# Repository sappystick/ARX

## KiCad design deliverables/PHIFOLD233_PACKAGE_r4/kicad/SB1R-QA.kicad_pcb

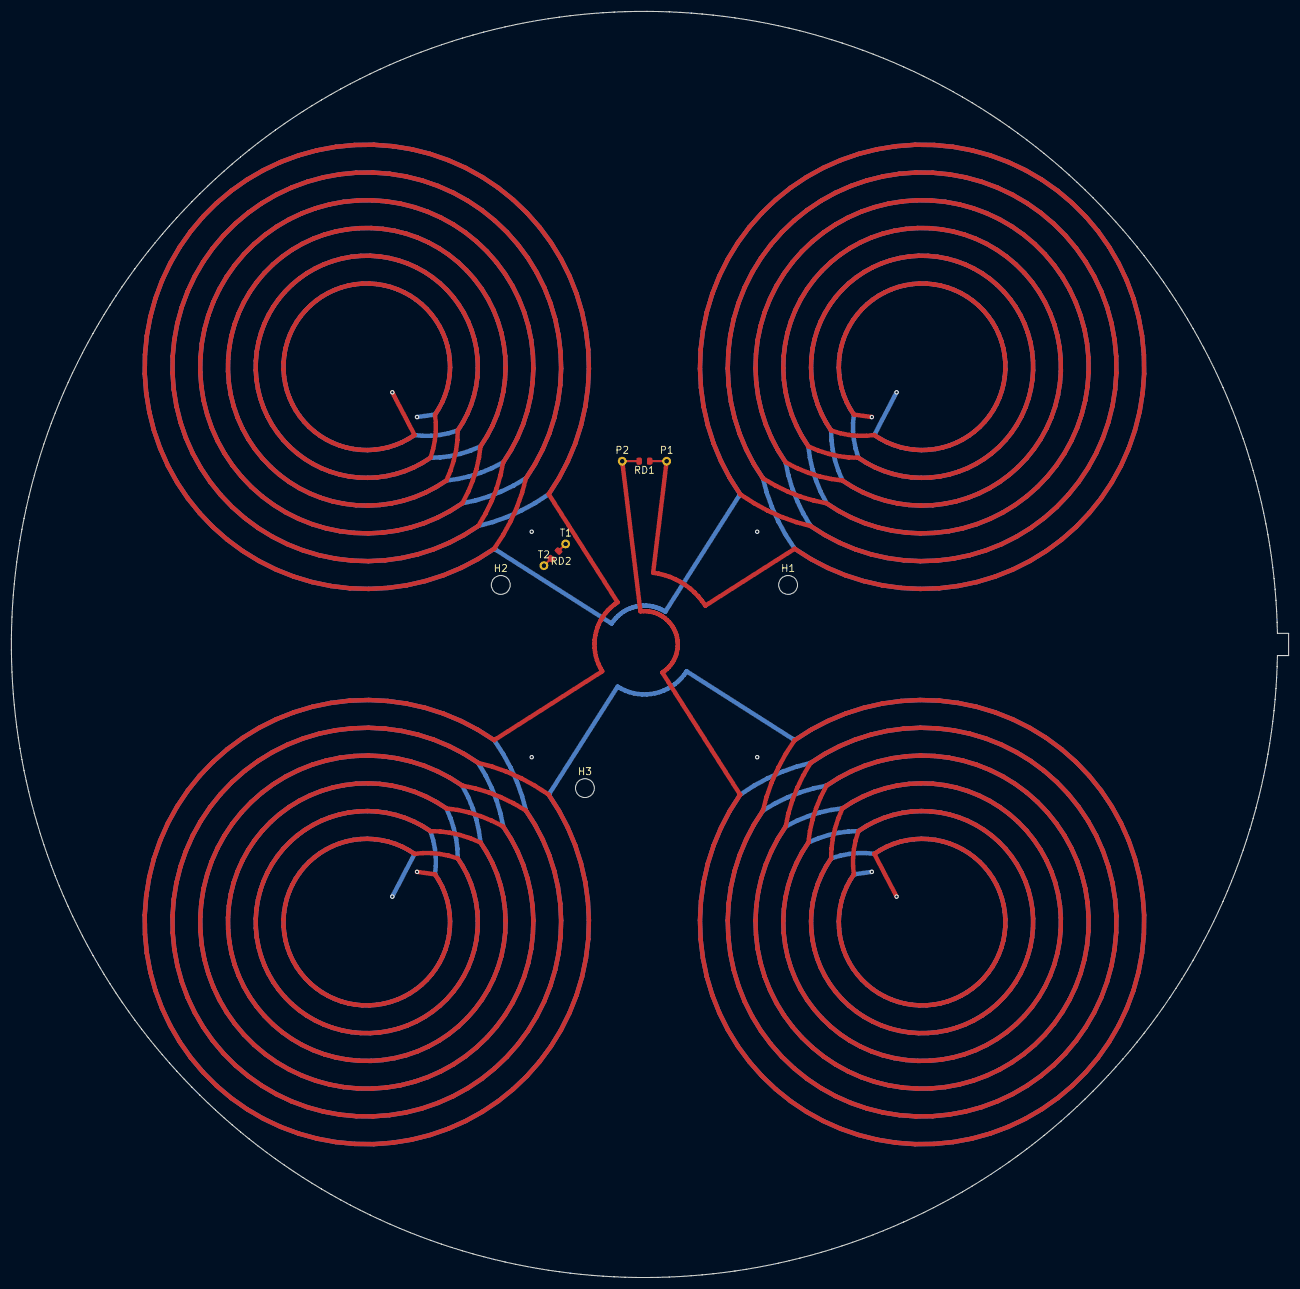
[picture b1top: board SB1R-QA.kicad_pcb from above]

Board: 4 copper layers, 230.0 x 228.0 mm, 9 parts (0 on the bottom side), 3 nets.

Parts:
H1, H2, H3: MH_M3
P1, P2: LEAD_PAD
RD1, RD2: 680R 0.1% thin film 0805, non-magnetic terminatio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; R_0805_2012Metric
T1, T2: TRANSFER_PAD

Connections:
QA_COIL: P1.1, P2.1, RD1.1, RD1.2
QB_T1: RD2.1, T1.1
QB_T2: RD2.2, T2.1

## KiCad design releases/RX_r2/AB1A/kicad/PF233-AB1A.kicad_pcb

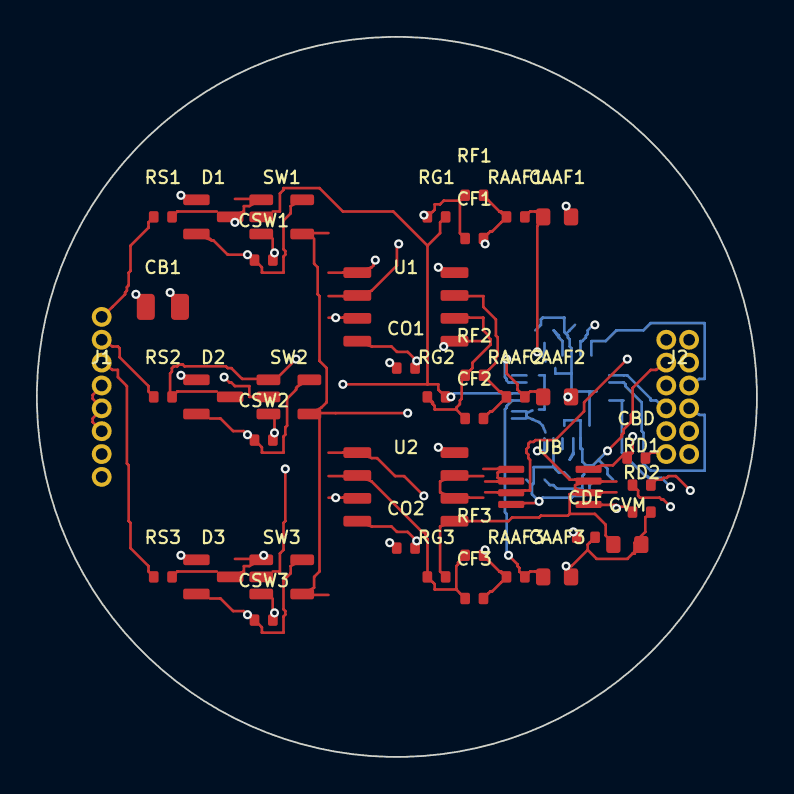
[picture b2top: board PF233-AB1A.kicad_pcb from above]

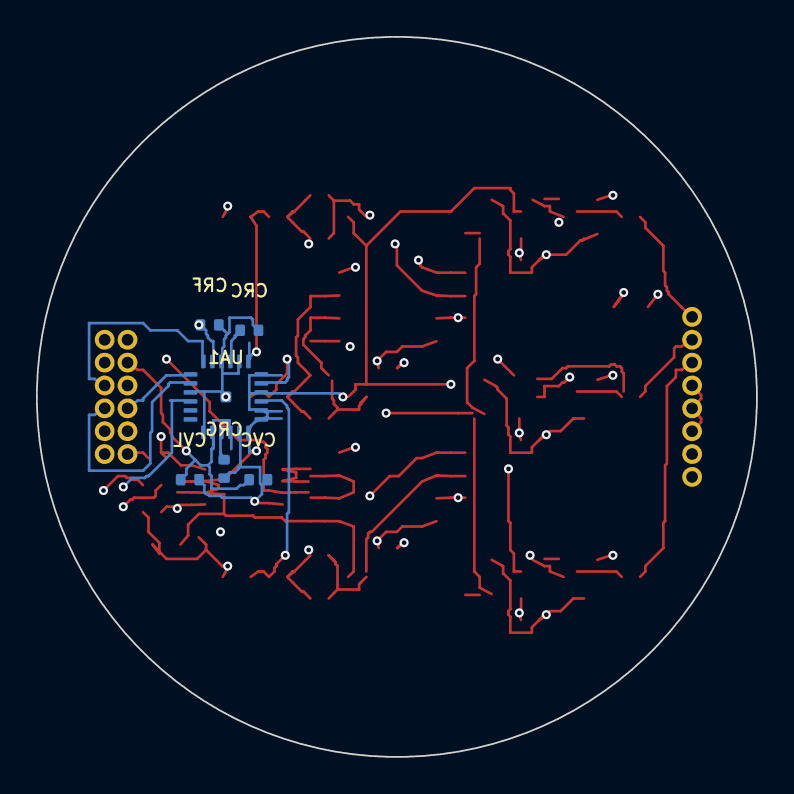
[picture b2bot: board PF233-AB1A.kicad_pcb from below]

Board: 6 copper layers, 40.0 x 40.0 mm, 46 parts (6 on the bottom side), 30 nets.

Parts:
CAAF1, CAAF2, CAAF3: 2n2; C_0603_1608Metric
CB1: 10u; C_0805_2012Metric
CBD: 100n; C_0402_1005Metric
CDF: 100n; C_0402_1005Metric
CF1, CF2, CF3: 22p; C_0402_1005Metric
CO1, CO2: 100n; C_0402_1005Metric
CRC: 100n; C_0402_1005Metric
CRF: 1u; C_0402_1005Metric
CRG: 1u; C_0402_1005Metric
CSW1, CSW2, CSW3: 100n; C_0402_1005Metric
CVC: 1u; C_0402_1005Metric
CVL: 1u; C_0402_1005Metric
CVM: 1u; C_0603_1608Metric
D1, D2, D3: BAV199; SOT-23
J1: Antenna harness 8p solder pads 1.27mm; PinHeader_1x8_P1.27mm
J2: Main-board 2x6 1.27mm header; PinHeader_2x6_P1.27mm
RAAF1, RAAF2, RAAF3: 200; R_0402_1005Metric
RD1, RD2: 100k; R_0402_1005Metric
RF1, RF2, RF3: 390; R_0402_1005Metric
RG1, RG2, RG3: 10; R_0402_1005Metric
RS1, RS2: 100; R_0402_1005Metric
RS3: 1000; R_0402_1005Metric
SW1, SW2, SW3: 74LVC1G66; SOT-23-5
U1, U2: OPA2211; SOIC-8_3.9x4.9mm_P1.27mm
UA1: AD7389-4; CP-24-25_ADI_LFCSP-24-1EP_4x4mm_P0.5mm_EP0.61x0.61mm
UB: OPA2365; MSOP-8_3x3mm_P0.65mm

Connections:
+3V3D: CVC.1, CVL.1, J2.3, UA1.2, UA1.4
+5VA: CB1.1, CBD.1, CO1.1, CO2.1, CSW1.1, CSW2.1, CSW3.1, D1.2, D2.2, D3.2, J2.1, SW1.5, SW2.5, SW3.5, U1.8, U2.8, UB.8
ADCIN_GX: CAAF1.1, RAAF1.2, UA1.13
ADCIN_GY: CAAF2.1, RAAF2.2, UA1.11
ADCIN_X8: CAAF3.1, RAAF3.2, UA1.9
BLANK: J2.10, SW1.4, SW2.4, SW3.4
CS: J2.6, UA1.18
FB_GX: CF1.1, RF1.1, RG1.1, U1.2
FB_GY: CF2.1, RF2.1, RG2.1, U1.6
FB_X8: CF3.1, RF3.1, RG3.1, U2.2
GND: CAAF1.2, CAAF2.2, CAAF3.2, CB1.2, CBD.2, CDF.2, CO1.2, CO2.2, CRC.2, CRF.2, CRG.2, CSW1.2, CSW2.2, CSW3.2, CVC.2, CVL.2, CVM.2, D1.1, D2.1, D3.1, J1.7, J1.8, J2.2, J2.4, J2.11, J2.12, RD2.2, SW1.3, SW2.3, SW3.3, U1.4, U2.4, UA1.1, UA1.5, UA1.14, UA1.16, UA1.21, UA1.25, UB.4
IN_GX: D1.3, RS1.2, SW1.1, U1.3
IN_GY: D2.3, RS2.2, SW2.1, U1.5
IN_X8: D3.3, RS3.2, SW3.1, U2.3
OUT_GX: CF1.2, RAAF1.1, RF1.2, U1.1
OUT_GY: CF2.2, RAAF2.1, RF2.2, U1.7
OUT_X8: CF3.2, RAAF3.1, RF3.2, U2.1
RAW_GX: J1.1, RS1.1
RAW_GY: J1.2, RS2.1
RAW_X8: J1.3, RS3.1
REFCAP: CRC.1, UA1.15
REGCAP: CRG.1, UA1.3
SCLK: J2.5, UA1.22
SDO1: J2.7, UA1.19
SDO2: J2.8, UA1.20
SPARE_OUT_U2: U2.6, U2.7
VCM: CVM.1, J1.4, J1.5, J1.6, RG1.2, RG2.2, RG3.2, SW1.2, SW2.2, SW3.2, U2.5, UA1.6, UA1.7, UA1.8, UA1.10, UA1.12, UB.6, UB.7
VCM_DIV: CDF.1, RD1.2, RD2.1, UB.5
VREF: UB.1, UB.2
VREF_RAW: CRF.1, RD1.1, UA1.17, UB.3

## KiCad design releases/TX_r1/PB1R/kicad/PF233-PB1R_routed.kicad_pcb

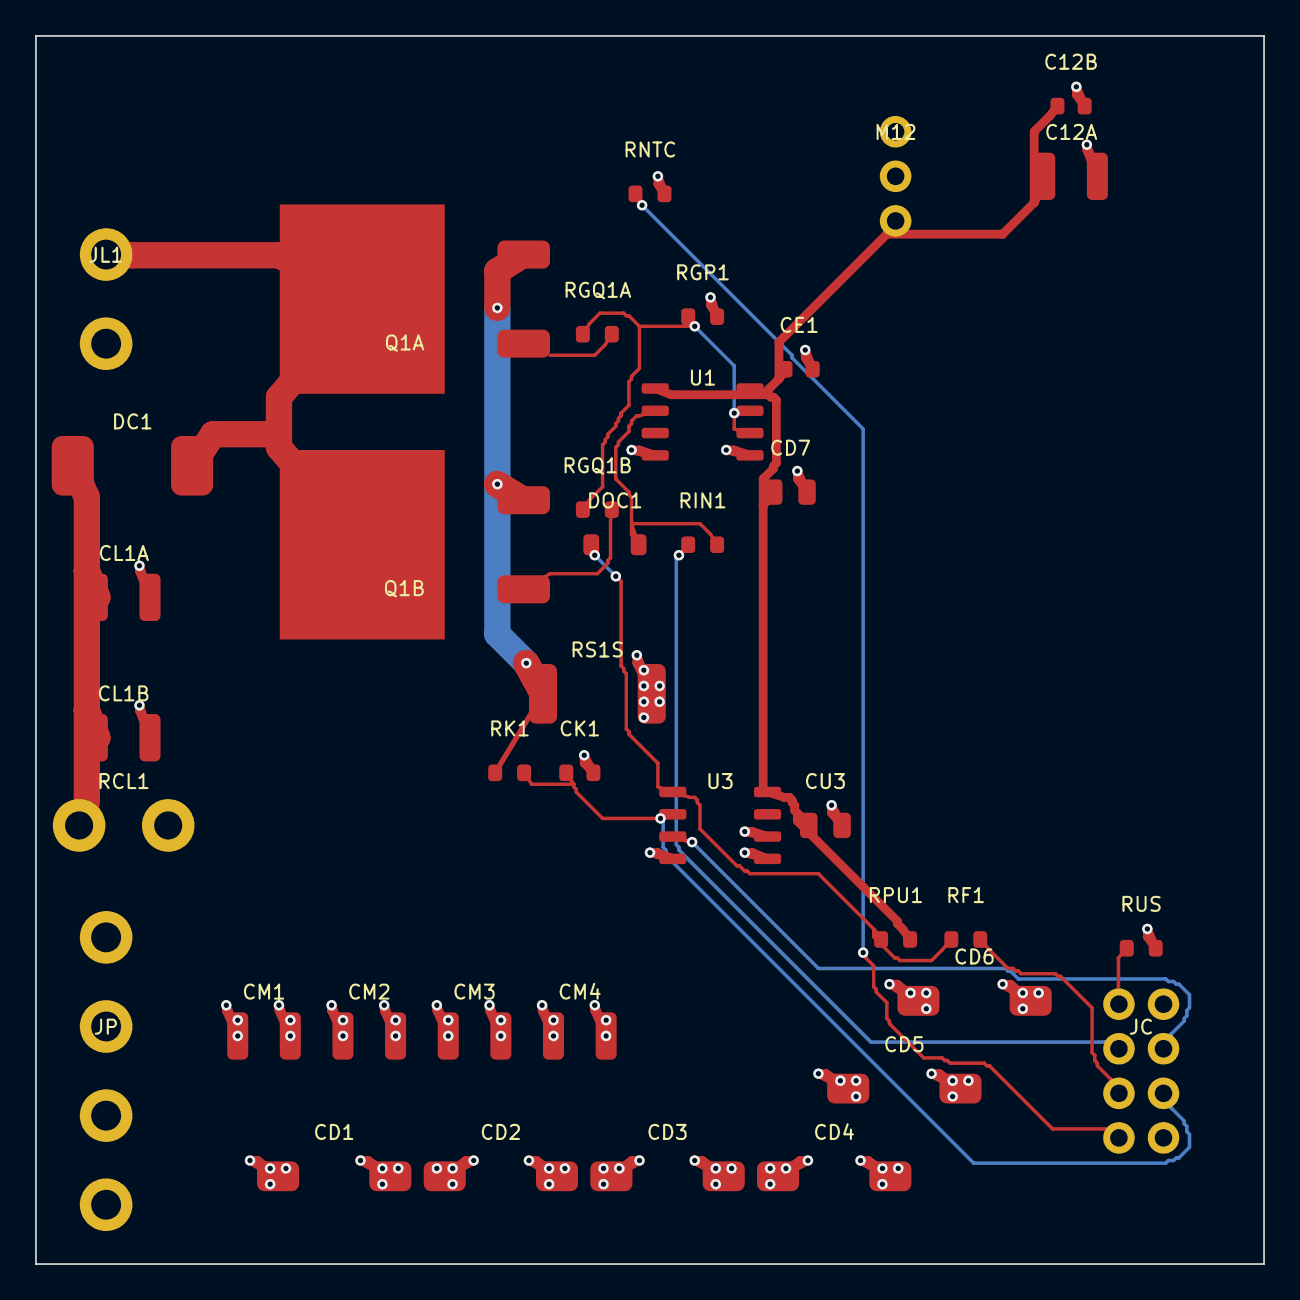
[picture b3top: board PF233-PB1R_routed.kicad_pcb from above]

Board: 4 copper layers, 70.0 x 70.0 mm, 39 parts (0 on the bottom side), 17 nets.

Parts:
C12A: 22u 25V; C_1210_3225Metric
C12B: 100n; C_0603_1608Metric
CD1, CD2, CD3, CD4, CD5, CD6: 150u 50V polymer Ta; CP_EIA-7343-43_Kemet-X
CD7: 1u 25V; C_0805_2012Metric
CE1: 100n; C_0603_1608Metric
CK1: 100p; C_0603_1608Metric
CL1A, CL1B: 100n 630V; C_1210_3225Metric
CM1, CM2, CM3, CM4: 10u 50V; C_1210_3225Metric
CU3: 1u 25V; C_0805_2012Metric
DC1: ES3J 600V 3A; D_SMC
DOC1: BAS16; D_SOD-123
JC: Umbilical from the head: SHLD GND TX1_IN REF_I1 F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; Pin_header_2x4_P2.54mm
JL1: Coil outer band: DRAIN, VBUS; Terminal_block_1x2_P5.08mm
JP: Power in: VBUS VBUS GND GND; Terminal_block_1x4_P5.08mm
M12: 12 V 1.5 A switching module; Converter_DCDC_Murata_OKI-78SR_Horizontal
Q1A, Q1B: 650V SJ 95mR; TO-263-3_TabPin2
RCL1: external 5k 10W (lid bank); SolderPad_2x_P5.08mm
RF1: 1k; R_0603_1608Metric
RGP1: 10k; R_0603_1608Metric
RGQ1A, RGQ1B: 10; R_0603_1608Metric
RIN1: 100; R_0603_1608Metric
RK1: 100; R_0603_1608Metric
RNTC: 10k NTC; R_0603_1608Metric
RPU1: 10k; R_0603_1608Metric
RS1S: 10m 3W; R_2512_6332Metric
RUS: 1M; R_0603_1608Metric
U1: TC4420; SOIC-8_3.9x4.9mm_P1.27mm
U3: LM393; SOIC-8_3.9x4.9mm_P1.27mm

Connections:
AUX12: C12A.1, C12B.1, CD7.1, CE1.1, CU3.1, M12.3, RPU1.2, U1.1, U1.8, U3.8
CLAMP1: CL1A.1, CL1B.1, DC1.1, RCL1.1
DRAIN1: DC1.2, JL1.1, Q1A.2, Q1B.2
DRVIN1: DOC1.2, RIN1.2, U1.2
FAULT1_N: JC.5, RF1.2
G1: RGP1.1, RGQ1A.1, RGQ1B.1, U1.6, U1.7
GATE_Q1A: Q1A.1, RGQ1A.2
GATE_Q1B: Q1B.1, RGQ1B.2
GND: C12A.2, C12B.2, CD1.2, CD2.2, CD3.2, CD4.2, CD5.2, CD6.2, CD7.2, CE1.2, CK1.2, CM1.2, CM2.2, CM3.2, CM4.2, CU3.2, JC.2, JC.8, JP.3, JP.4, M12.2, RGP1.2, RNTC.2, RS1S.2, RUS.2, U1.4, U1.5, U3.4, U3.5, U3.6
ISENSE1: CK1.1, JC.6, RK1.2, U3.2
NTC_SENSE: JC.7, RNTC.1
OC1_OUT: DOC1.1, RF1.1, RPU1.1, U3.1
REF_I1: JC.4, U3.3
SRC1: Q1A.3, Q1B.3, RK1.1, RS1S.1
TX1_IN: JC.3, RIN1.1
UMB_SHLD: JC.1, RUS.1
VBUS: CD1.1, CD2.1, CD3.1, CD4.1, CD5.1, CD6.1, CL1A.2, CL1B.2, CM1.1, CM2.1, CM3.1, CM4.1, JL1.2, JP.1, JP.2, M12.1, RCL1.2

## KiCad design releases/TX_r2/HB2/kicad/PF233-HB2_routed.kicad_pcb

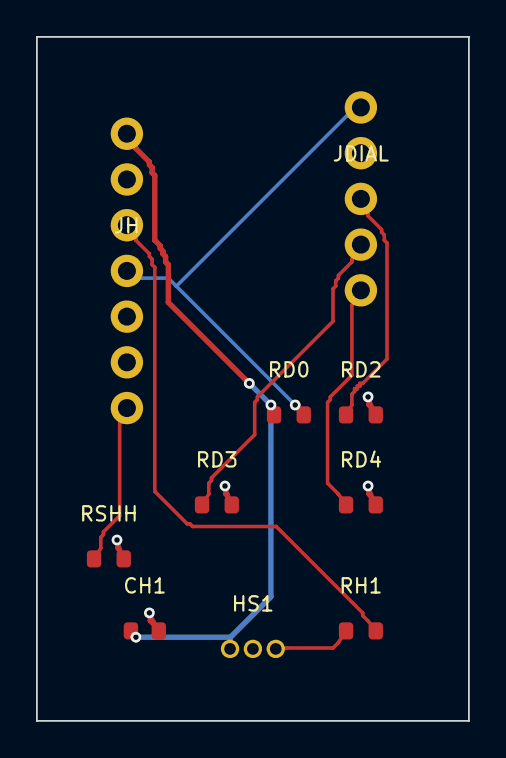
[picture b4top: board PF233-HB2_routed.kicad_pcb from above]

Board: 4 copper layers, 24.0 x 38.0 mm, 10 parts (0 on the bottom side), 9 nets.

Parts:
CH1: 100n; C_0603_1608Metric
HS1: DRV5023BIQLPG; TO-92_Inline
JDIAL: Dial: COM P1 P2 P3 P4 (4-pos rotary, top housing); Pin_header_1x5_P2.54mm
JH: Signal cord to the head: +3V3 GND TRIG DIAL - - S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; Pin_header_1x7_P2.54mm
RD0, RD3: 10k; R_0603_1608Metric
RD2: 3k3; R_0603_1608Metric
RD4: 33k; R_0603_1608Metric
RH1: 1k; R_0603_1608Metric
RSHH: 0R; R_0603_1608Metric

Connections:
DIAL: JDIAL.1, JH.4, RD0.2
DP2: JDIAL.3, RD2.1
DP3: JDIAL.4, RD3.1
DP4: JDIAL.5, RD4.1
GND: CH1.2, HS1.2, JDIAL.2, JH.2, RD2.2, RD3.2, RD4.2, RSHH.2
HALL_OUT: HS1.3, RH1.1
P3V3: CH1.1, HS1.1, JH.1, RD0.1
SHIELD: JH.7, RSHH.1
TRIG: JH.3, RH1.2

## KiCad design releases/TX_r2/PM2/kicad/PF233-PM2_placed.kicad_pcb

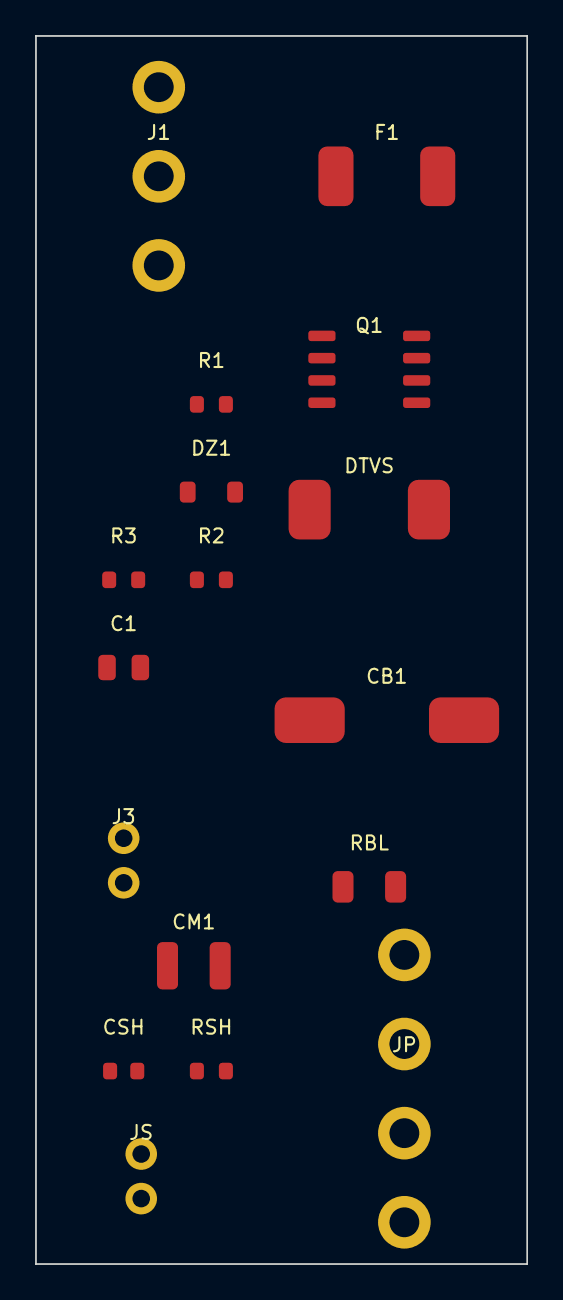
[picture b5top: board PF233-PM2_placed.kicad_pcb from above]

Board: 4 copper layers, 28.0 x 70.0 mm, 17 parts (0 on the bottom side), 9 nets, no tracks yet.

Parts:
C1: 220n 50V; C_0805_2012Metric
CB1: 470u 50V; CP_Elec_10x10
CM1: 10u 50V; C_1210_3225Metric
CSH: 1n 100V; C_0603_1608Metric
DTVS: SMCJ33A; D_SMC
DZ1: 15V zener; D_SOD-123
F1: 5A slow 32V; Fuse_1812_4532Metric
J1: MT60-M leads: BAT+ BAT- ILK; Wire_pads_1x3_P5.08mm
J3: Power switch pair (top housing); Wire_pads_1x2_P2.54mm
JP: Power cord: VBUS VBUS GND GND; Wire_pads_1x4_P5.08mm
JS: Shields: power-cord braid, septum Cu mesh; Wire_pads_1x2_P2.54mm
Q1: P-MOSFET -40V; SOIC-8_3.9x4.9mm_P1.27mm
R1: 47k; R_0603_1608Metric
R2: 68k; R_0603_1608Metric
R3: 1k; R_0603_1608Metric
RBL: 100k; R_1206_3216Metric
RSH: 1M; R_0603_1608Metric

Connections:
BAT_F: DZ1.1, F1.2, Q1.1, Q1.2, Q1.3, R1.1
BAT_P: F1.1, J1.1
GND: CB1.2, CM1.2, CSH.2, DTVS.2, J1.2, JP.3, JP.4, RBL.2, RSH.2
ILK: J1.3, J3.2
Q1_G: DZ1.2, Q1.4, R1.2, R2.1, R3.1
SHIELD: CSH.1, JS.1, JS.2, RSH.1
SS: C1.1, R3.2
SW_A: J3.1, R2.2
VBUS: C1.2, CB1.1, CM1.1, DTVS.1, JP.1, JP.2, Q1.5, Q1.6, Q1.7, Q1.8, RBL.1
